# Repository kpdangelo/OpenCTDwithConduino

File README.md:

# OpenCTDwithConduino
OpenCTD with a low cost Conduino conductivity sensor

This has drift issues, see https://github.com/kpdangelo/OpenCTD-Conduino-K1.0 

*********************************************************************************************************************************************
This version is the basic design. During testing, a major drift in the reading was discovered. Two revisions were made, with some improvement. Continuing research is being done on Version 3 - see a separate entry for that, OpenCTDwithConduinoV3.
*********************************************************************************************************************************************

This project merges the Oceanography for Everyone Open CTD with the Conduino conductivity sensor.

Open CTD:
https://github.com/OceanographyforEveryone/OpenCTD

Conduino:
Marco Carminati, Paolo Luzzatto-Fegiz,
Conduino: Affordable and high-resolution multichannel water conductivity sensor using micro USB connectors,
In Sensors and Actuators B: Chemical, Volume 251, 2017, Pages 1034-1041, ISSN 0925-4005,
https://doi.org/10.1016/j.snb.2017.05.184.

Follow the basic assembly instructions from OpenCTD along with the included instructions for constructing
a Conduino.

PCBs can be ordered from OSHPARK, or Eagle and Gerber files are included here.

The system goes into a 2" PVC pipe and seals with Marine Epoxy and a 3D printed plug (file included here). 
See Conduino Pipe Assembly.pdf file.

First test was taking it into the surf and turbulence here at Spanish Bay for a few minutes, see excel file for that gem.

March 25, 2018

3/27/18
slight modification to the schematic to take away the filter on the network analyzer buffer (C5 and R3). It was giving a gigantic time constant to the measurement.

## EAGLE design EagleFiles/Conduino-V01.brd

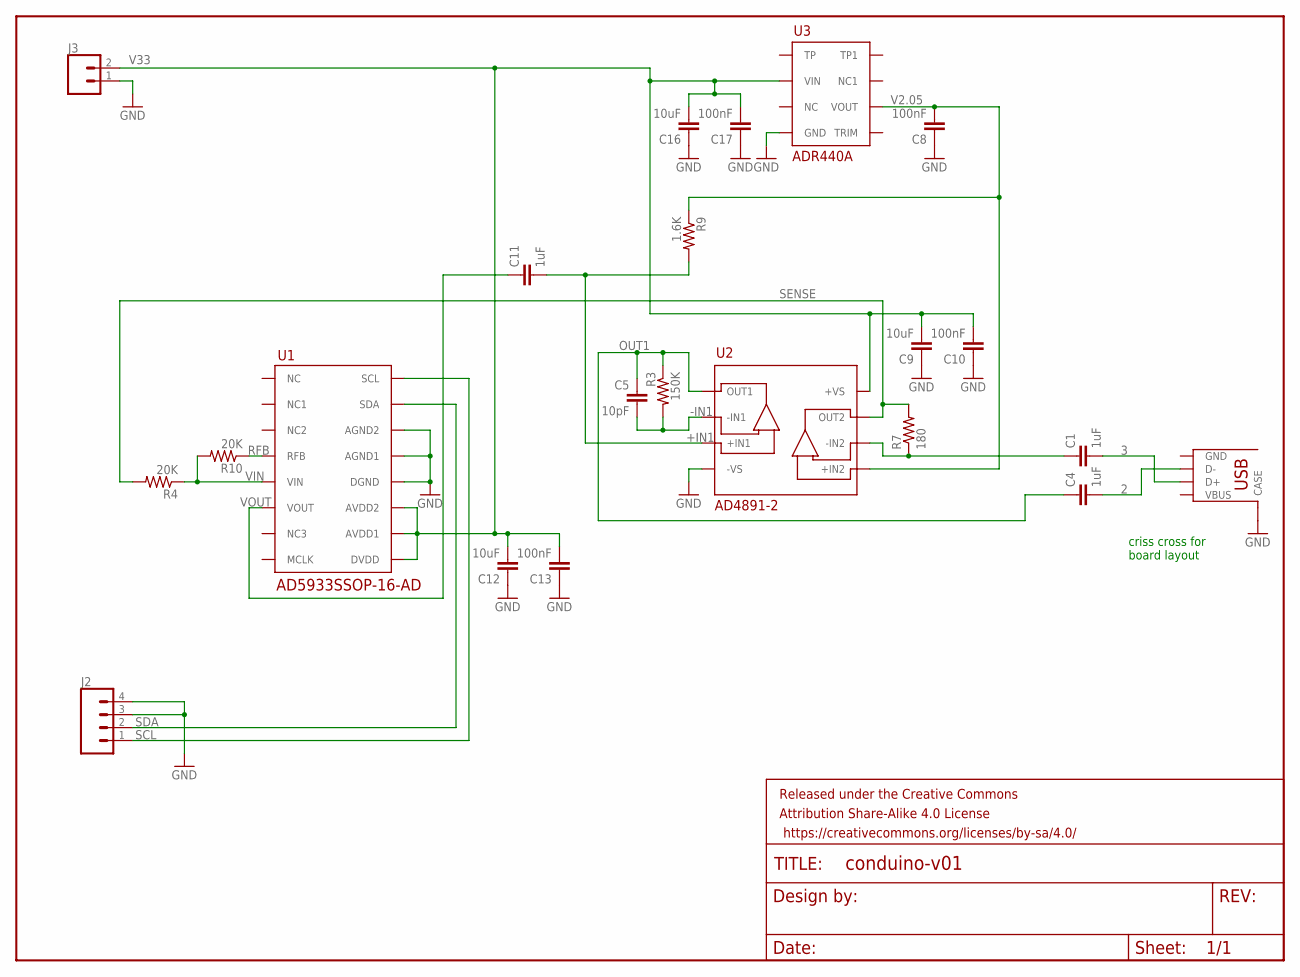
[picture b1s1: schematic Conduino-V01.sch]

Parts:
C1, C4, C11: 1uF; 0603-CAP
C5: 10pF; 0603-CAP
C8, C10, C13, C17: 100nF; 0603-CAP
C9, C12, C16: 10uF; 0603-CAP
FRAME1: FRAME-LETTER; CREATIVE_COMMONS
J1: USBA-SIDE
J2: CONN_041X04_NO_SILK; 1X04_NO_SILK
J3: CONN_021X02_NO_SILK; 1X02_NO_SILK
R3: 150K; 0603-RES
R4, R10: 20K; 0603-RES
R7: 180; 0603-RES
R9: 1.6K; 0603-RES
U1: AD5933SSOP-16-AD; SSOP-16-AD
U2: AD4891-2; SOIC_N
U3: ADR440A; SOIC_N

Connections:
2: C4.2, J1.P$2 (D-)
3: C1.2, J1.P$3 (D+)
+IN1: C11.2, R9.2, U2.P$3 (+IN1)
-IN1: C5.2, R3.2, U2.P$2 (-IN1)
-IN2: C1.1, R7.1, U2.P$6 (-IN2)
GND: C8.1, C9.1, C10.1, C12.1, C13.1, C16.1, C17.1, J1.P$5 (CASE), J1.P$6 (CASE), J2.3, J2.4, J3.1, U1.P$12 (DGND), U1.P$13 (AGND1), U1.P$14 (AGND2), U2.P$4 (-VS), U3.P$4 (GND)
OUT1: C4.1, C5.1, R3.1, U2.P$1 (OUT1)
RFB: R10.1, U1.P$4 (RFB)
SCL: J2.1, U1.P$16 (SCL)
SDA: J2.2, U1.P$15 (SDA)
SENSE: R4.2, R7.2, U2.P$7 (OUT2)
V2.05: C8.2, R9.1, U2.P$5 (+IN2), U3.P$6 (VOUT)
V33: C9.2, C10.2, C12.2, C13.2, C16.2, C17.2, J3.2, U1.P$9 (DVDD), U1.P$10 (AVDD1), U1.P$11 (AVDD2), U2.P$8 (+VS), U3.P$2 (VIN)
VIN: R4.1, R10.2, U1.P$5 (VIN)
VOUT: C11.1, U1.P$6 (VOUT)

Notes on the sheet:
criss cross for board layout

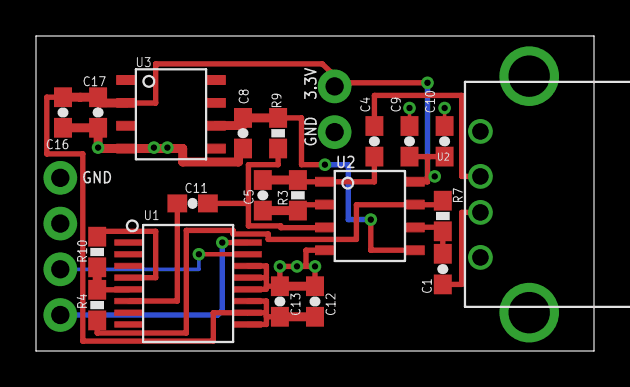
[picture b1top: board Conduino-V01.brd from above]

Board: 2 copper layers, 31.0 x 17.5 mm, 23 parts (0 on the bottom side), 15 nets.

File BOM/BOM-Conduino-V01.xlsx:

Conduino Partslist
PCB can be ordered directly from OSHPARK
Part | Value | Device | Package | Description | Cost (single) | link
C1 | 1uF | CAP0603-CAP | 0603-CAP | Capacitor | 0.22 | https://www.digikey.com/product-detail/en/murata-electronics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
C4 | 1uF | CAP0603-CAP | 0603-CAP | Capacitor | 0.22
C5 | 10pF | CAP0603-CAP | 0603-CAP | Capacitor | 0.28999999999999998 | https://www.digikey.com/product-detail/en/kemet/C0603C100J8G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
C8 | 100nF | CAP0603-CAP | 0603-CAP | Capacitor | 0.38 | https://www.digikey.com/product-detail/en/avx-corporation/08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
C9 | 10uF | CAP0603-CAP | 0603-CAP | Capacitor | 0.15 | https://www.digikey.com/product-detail/en/taiyo-yuden/LMK212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
C10 | 100nF | CAP0603-CAP | 0603-CAP | Capacitor | 0.38
C11 | 1uF | CAP0603-CAP | 0603-CAP | Capacitor | 0.22
C12 | 10uF | CAP0603-CAP | 0603-CAP | Capacitor | 0.15
C13 | 100nF | CAP0603-CAP | 0603-CAP | Capacitor | 0.38
C16 | 10uF | CAP0603-CAP | 0603-CAP | Capacitor | 0.15
C17 | 100nF | CAP0603-CAP | 0603-CAP | Capacitor | 0.38
J1 | USBA-SIDE | USBA-SIDE | USBA-SIDE | USB Port | 0.4 | https://www.digikey.com/product-detail/en/amphenol-commercia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
J2 | Connector | 1X04 Header |  | Connector |  | use 0.1 mil headers
J3 | Connector | 1X02 header |  | Connector
R3 | 150K | RESISTOR0603-RES | 0603-RES | 1E-3 | 0.35 | https://www.digikey.com/product-detail/en/panasonic-electron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
R4 | 20K | RESISTOR0603-RES | 0603-RES | 1E-3 | 0.39 | https://www.digikey.com/product-detail/en/yageo/RT0805BRD072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
R7 | 180 | RESISTOR0603-RES | 0603-RES | 1E-3 | 0.35 | https://www.digikey.com/product-detail/en/panasonic-electron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
R9 | 1.6K | RESISTOR0603-RES | 0603-RES | 0.01 | 0.1 | https://www.digikey.com/product-detail/en/panasonic-electron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
R10 | 20K | RESISTOR0603-RES | 0603-RES | 1E-3 | 0.39
U1 | AD5933SSOP-16-AD | AD5933SSOP-16-AD | SSOP-16-AD | Network Analyzer | 36.32 | https://www.digikey.com/product-detail/en/analog-devices-inc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
U2 | AD4891-2 | AD4891-2 | SOIC_N | Op Amps | 2.09 | https://www.digikey.com/product-detail/en/analog-devices-inc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
U3 | ADR440A | ADR440A | SOIC_N | Voltage Reference | 6.32 | https://www.digikey.com/product-detail/en/analog-devices-inc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
PCB |  |  |  | Conduino PCB | 1.4 | https://www.oshpark.com/shared_projects/yAFaZZxk
 |  |  |  |  | 51.03

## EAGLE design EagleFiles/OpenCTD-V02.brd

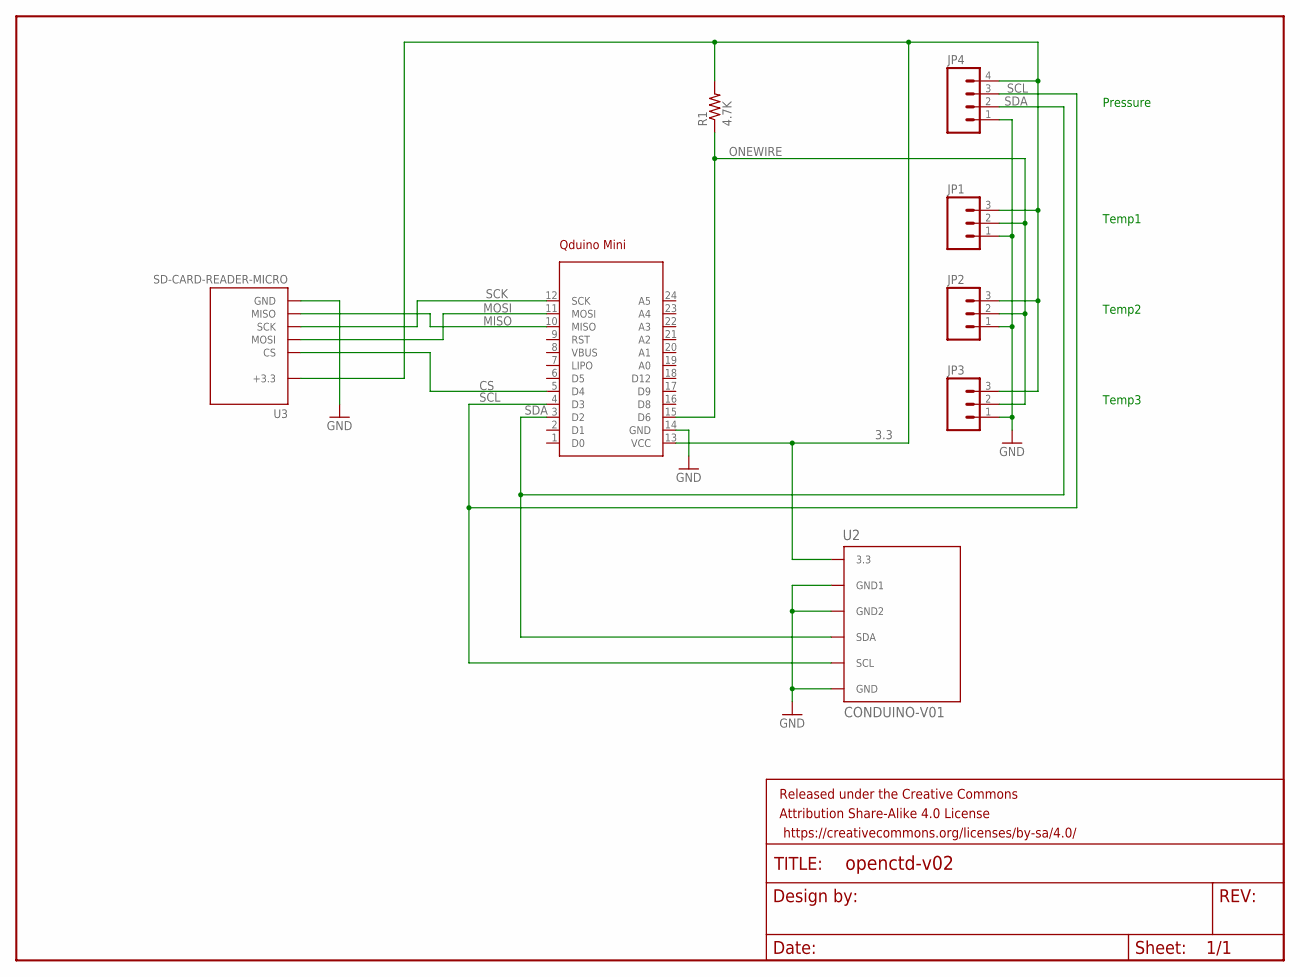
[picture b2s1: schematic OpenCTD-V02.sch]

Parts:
FRAME1: FRAME-LETTER; CREATIVE_COMMONS
JP1, JP2, JP3: M031X03_NO_SILK; 1X03_NO_SILK
JP4: M041X04_NO_SILK; 1X04_NO_SILK
R1: 4.7K; AXIAL-0.4
U1: QDUINO_MINI
U2: CONDUINO-V01
U3: SD-CARD-READER-MICRO; MICROSD_MOLEX

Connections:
3.3: JP1.3, JP2.3, JP3.3, JP4.4, R1.P$2 (2), U1.13 (VCC), U2.6 (3.3), U3.P$4 (+3.3)
CS: U1.5 (D4), U3.P$2 (CS)
GND: JP1.1, JP2.1, JP3.1, JP4.1, U1.14 (GND), U2.3 (GND), U2.4 (GND1), U2.5 (GND2), U3.P$6 (GND), U3.P$9 (GND), U3.P$10 (GND), U3.P$11 (GND), U3.P$12 (GND)
MISO: U1.10 (MISO), U3.P$7 (MISO)
MOSI: U1.11 (MOSI), U3.P$3 (MOSI)
ONEWIRE: JP1.2, JP2.2, JP3.2, R1.P$1 (1), U1.15 (D6)
SCK: U1.12 (SCK), U3.P$5 (SCK)
SCL: JP4.3, U1.4 (D3), U2.1 (SCL)
SDA: JP4.2, U1.3 (D2), U2.2 (SDA)

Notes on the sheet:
Pressure
Temp1
Temp2
Temp3

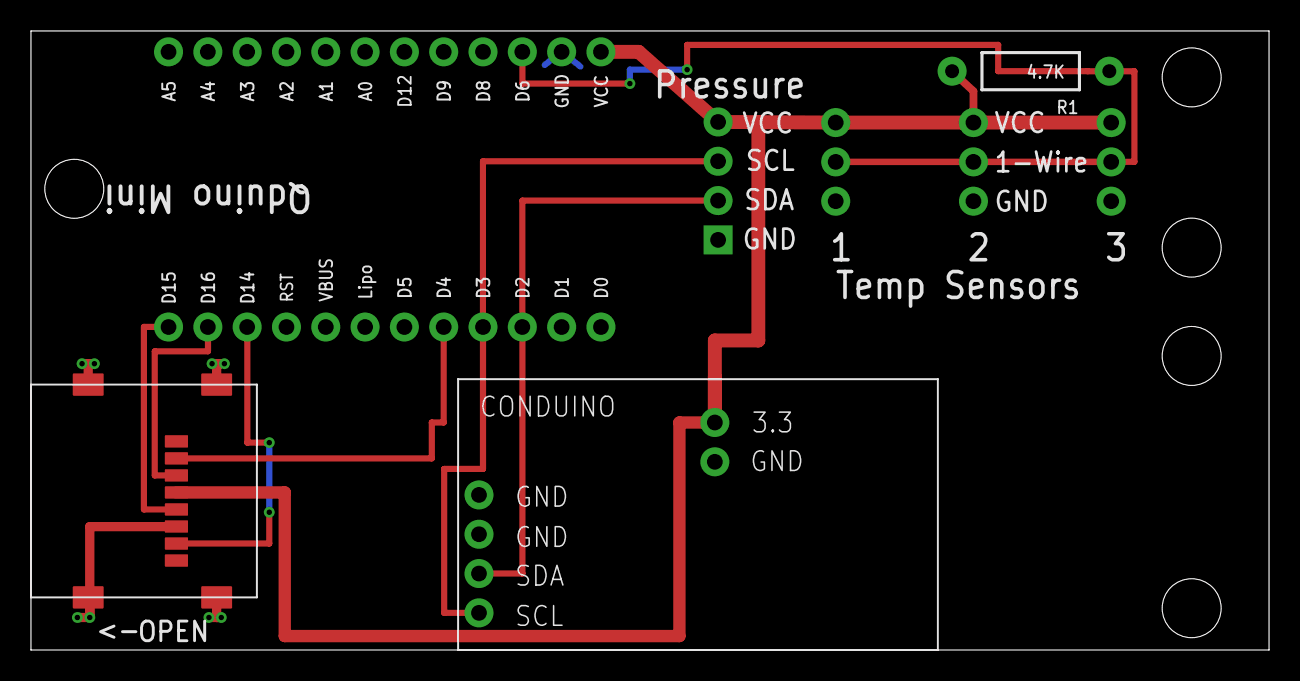
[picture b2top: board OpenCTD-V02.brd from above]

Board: 2 copper layers, 80.0 x 40.0 mm, 9 parts (0 on the bottom side), 9 nets.

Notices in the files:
parts and their libraries:
SparkFun-Aesthetics: Licensing: Creative Commons ShareAlike 4.0 International - https://creativecommons.org/licenses/by-sa/4.0
SparkFun-Aesthetics: Released under the Creative Commons
SparkFun-Aesthetics: https://creativecommons.org/licenses/by-sa/4.0
